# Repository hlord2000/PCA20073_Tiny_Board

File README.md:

# PCA20073 Tiny Board - nRF54L15 Coin Cell Board 
A very small demo board showing the solution size of Nordic's nRF54L15 in chip-scale package.
Alongside our components are our partners' products: **SiTime's** <0.5x0.5mm MEMS resonator, **Ignion's** 3x2mm 2.4G-10.6Hz chip antenna, **Analog Device's** new micropower 3-axis accelerometer

## Key components

| Reference Designator | Part Number        | Description                                                                                                |
|----------------------|--------------------|------------------------------------------------------------------------------------------------------------|
| U1                   | nRF54L15-CAAA      | [Nordic Semiconductor nRF54L15 Series - Advanced multiprotocol System-on-Chip (SoC) supporting Bluetooth Low Energy, ANT, 802.15.4, Thread, Zigbee, and proprietary 2.4 GHz protocols.](https://www.nordicsemi.com/Products/nRF54L15) |
| Y2                   | SiT11100-B6-032.0000-E6035-T325 | [SiTime ultra-small 0505 Size 32 MHz MEMS Resonator](https://www.sitime.com/products/resonators/mhz-mems-resonators/sit11100)     |
| AE1                  | NN02-101           | [Ignion NANO mXTEND - Ultra-small 2.4GHz chip antenna utilizing Virtual Antenna® technology.](https://ignion.io/product/nano-mxtend/)                |
| U3                   | ADXL366            | [Analog Devices ADXL366 - Micropower, 3-Axis, ±2g/±4g/±8g Digital Output MEMS Accelerometer.](https://www.analog.com/en/products/adxl366.html)                |

## System Features
- Low Vf blue LED for indication
- Tag-Connect TC2030 for debug port
- UART TX/RX pads for testing
- Jumper for system power characterization using the [PPK2](https://www.nordicsemi.com/Products/Development-hardware/Power-Profiler-Kit-2)

## Possible Usecases
- BLE Beacon
- Channel sounding reflector

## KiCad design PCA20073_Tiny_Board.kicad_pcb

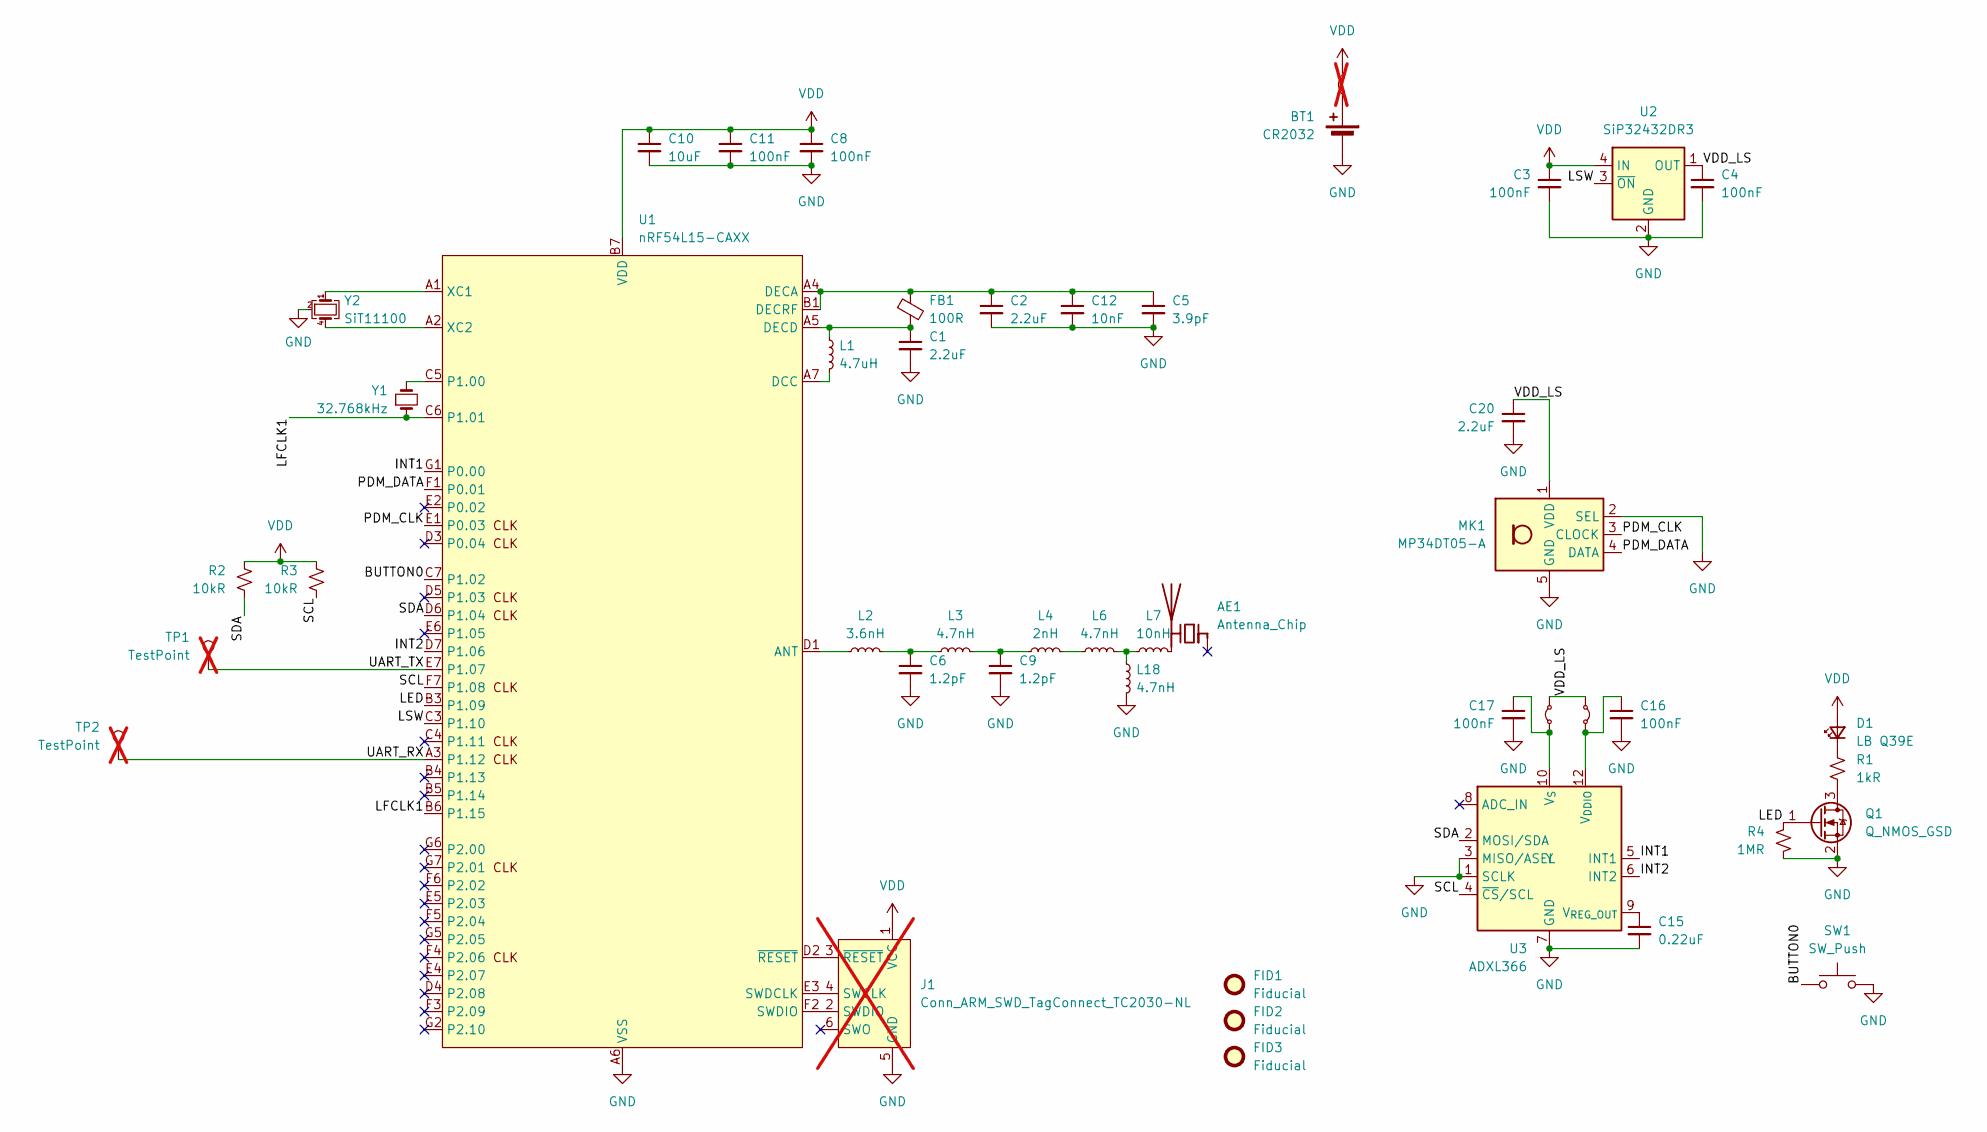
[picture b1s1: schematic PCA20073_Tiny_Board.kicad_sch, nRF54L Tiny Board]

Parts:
AE1: Antenna_Chip; Ignion_NN02-101; PartId 100700079
BT1: CR2032; BatteryHolder_Multicomp_BC-2001_1x2032; PartId 100500047; LCSC C964829
C1, C2, C20: 2.2uF; C_0201_0603Metric; PartId 100200660; LCSC C23630
C3, C4, C8, C11, C16, C17: 100nF; C_0201_0603Metric; PartId 100200469; LCSC C76939
C5: 3.9pF; C_0201_0603Metric; PartId 100200424; LCSC C22374845
C6, C9: 1.2pF; C_0201_0603Metric; PartId 100200086; LCSC C85895
C10: 10uF; C_0402_1005Metric; PartId 100200383; LCSC C15525
C12: 10nF; C_0201_0603Metric; PartId 100200491; LCSC C76941
C15: 0.22uF; C_0201_0603Metric; PartId 100200487; LCSC C701263
D1: LB Q39E; LED_0603_1608Metric; PartId 101400142; LCSC C84273
FB1: 100R; C_0201_0603Metric; PartId 100300419; LCSC C83991
FID1, FID2, FID3: Fiducial; Fiducial_0.5mm_Mask1mm
J1: Conn_ARM_SWD_TagConnect_TC2030-NL; Tag-Connect_TC2030-IDC-NL_2x03_P1.27mm_Vertical; not fitted
JP1: Jumper_2_Small_Bridged; SolderJumper-2_P1.3mm_Bridged_RoundedPad1.0x1.5mm; not fitted
JP2, JP3: Jumper_2_Small_Bridged; R_0402_1005Metric; PartId 100100109; LCSC C17168
L1: 4.7uH; L_0402_1005Metric; PartId 100300441
L2: 3.6nH; L_0201_0603Metric; PartId 100300223; LCSC C275212
L3, L6, L18: 4.7nH; L_0201_0603Metric; PartId 100300231; LCSC C86126
L4: 2nH; L_0201_0603Metric; PartId 100300016; LCSC C307709
L7: 10nH; L_0201_0603Metric; PartId 100300242; LCSC C162594
MK1: MP34DT05-A; ST_HCLGA-4_3x4mm_P1.35mm; PartId MP34DT05-A
Q1: Q_NMOS_GSD; Diodes_DFN1006-3; PartId 101300187; LCSC C7527987
R1: 1kR; R_0402_1005Metric; PartId 100100171; LCSC C106235
R2, R3: 10kR; R_0201_0603Metric; PartId 100100065; LCSC C106225
R4: 1MR; R_0402_1005Metric; PartId 100100265; LCSC C138033
SW1: SW_Push; SW_Push_1P1T_NO_Vertical_Wuerth_434133025816; PartId 101500104; LCSC C127488
TP1, TP2: TestPoint; TestPoint_Pad_D1.0mm; not fitted
U1: nRF54L15-CAXX; BGA-47_7x7_2.451x2.245mm; PartId 102000283
U2: SiP32432DR3; SOT-363_SC-70-6; PartId SiP32432DR3; LCSC C141606
U3: ADXL366; Analog_LGA-12_2.20x2.30mm_P0.5mm; PartId ADXL366
Y1: 32.768kHz; Crystal_SMD_1210-2Pin_1.2x1.0mm; PartId ECS-.327-9-1210-TR
Y2: SiT11100; Oscillator_SMD_SiTime_SiT11100-4Pin_0.46x0.46mm; PartId SiT11100

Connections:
/BUTTON0: SW1.1, U1.C7 (P1.02)
/INT1: U1.G1 (P0.00), U3.5 (INT1)
/INT2: U1.D7 (P1.06), U3.6 (INT2)
/LED: Q1.1 (G), R4.1, U1.B3 (P1.09)
/LFCLK1: U1.B6 (P1.15), U1.C6 (P1.01), Y1.1
/LSW: U1.C3 (P1.10), U2.3 (~ON)
/PDM_CLK: MK1.3 (CLOCK), U1.E1 (P0.03)
/PDM_DATA: MK1.4 (DATA), U1.F1 (P0.01)
/SCL: R3.2, U1.F7 (P1.08), U3.4 (~CS/SCL)
/SDA: R2.2, U1.D6 (P1.04), U3.2 (MOSI/SDA)
/UART_RX: TP2.1, U1.A3 (P1.12)
/UART_TX: TP1.1, U1.E7 (P1.07)
/VDD_LS: C4.1, C20.1, JP2.2 (B), JP3.2 (B), MK1.1 (VDD), U2.1 (OUT)
GND: BT1.2 (-), C1.2, C2.2, C3.2, C4.2, C5.2, C6.2, C8.2, C9.2, C10.2, C11.2, C12.2, C15.2, C16.2, C17.2, C20.2, J1.5 (GND), L18.2, MK1.2 (SEL), MK1.5 (GND), Q1.2 (S), R4.2, SW1.2, U1.A6 (VSS), U1.C2 (VSS_PA), U1.G4 (VSS), U2.2 (GND), U2.5 (GND), U3.1 (SCLK), U3.3 (MISO/ASEL), U3.7 (GND), U3.11 (GND), Y2.2, Y2.3
unnamed: AE1.2 (PCB_Trace), L7.2
unnamed: BT1.1 (+), JP1.1 (A)
unnamed: C6.1, L2.2, L3.1
unnamed: C9.1, L3.2, L4.1
unnamed: D1.1 (K), R1.1
unnamed: J1.4 (SWCLK), U1.E3 (SWDCLK)
unnamed: J1.2 (SWDIO), U1.F2 (SWDIO)
unnamed: J1.3 (~RESET), U1.D2 (~RESET)
unnamed: C16.1, JP2.1 (A), U3.12 (V_{DDIO})
unnamed: C17.1, JP3.1 (A), U3.10 (V_{S})
unnamed: L4.2, L6.1
unnamed: L6.2, L7.1, L18.1
unnamed: Q1.3 (D), R1.2
unnamed: L2.1, U1.D1 (ANT)
unnamed: L1.2, U1.A7 (DCC)
unnamed: C2.1, C5.1, C12.1, FB1.1, U1.A4 (DECA), U1.B1 (DECRF)
unnamed: C1.1, FB1.2, L1.1, U1.A5 (DECD)
unnamed: U1.C5 (P1.00), Y1.2
unnamed: U1.A1 (XC1), Y2.1
unnamed: U1.A2 (XC2), Y2.4
unnamed: C15.1, U3.9 (V_{REG_OUT})
VDD: C3.1, C8.1, C10.1, C11.1, D1.2 (A), J1.1 (VCC), JP1.2 (B), R2.1, R3.1, U1.B7 (VDD), U1.G3 (VDD), U2.4 (IN)

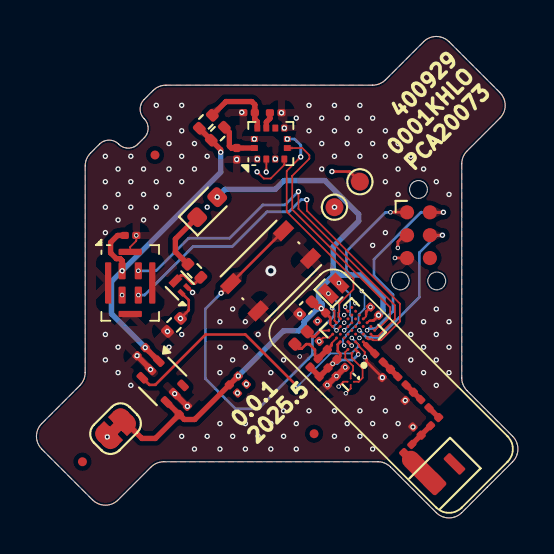
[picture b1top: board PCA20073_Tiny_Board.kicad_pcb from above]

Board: 4 copper layers, 26.7 x 26.7 mm, 47 parts (1 on the bottom side), 36 nets.

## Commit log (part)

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2024-10-29 Initial commit.
2024-10-30 Routing complete
2024-11-07 Nov. 7th 2024
2024-12-09 Dec92024
2024-12-24 Update Dec. 24
2025-01-31 Updated for production
2025-01-31 Added production panel files
2025-01-31 Added panel jan 31 2025
2025-02-03 Fixed issues w/ mousebites, added stitching vias, added fiducials
2025-02-24 Added latest production files
2025-05-09 Reworked SiT11100 footprint
